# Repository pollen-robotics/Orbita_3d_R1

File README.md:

# Orbita_3d_R1
All you need to make your own Orbita_3d Joint!

## Basically
Please find:
 - Electronic boards that controls (elec_Houston), drives (elec_Major_Tom) and measures (elec_Pacman) the Orbita 3d Joint over 12V-supplied Dynamixel bus.
 - Firmware gather communication (Dynamixel library) and motor control (SimpleFOC library)
 - Cables

## Licences
 - Firmware is under Apache-2.0 licence
 - Electronic/Cables is under CC-BY-SA-NC Licence

## Patents
https://patents.google.com/patent/FR3141363A1

## Contact
contact@pollen-robotics.com

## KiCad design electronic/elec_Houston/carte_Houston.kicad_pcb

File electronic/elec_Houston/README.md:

# Houston Electronic Board

Houston board is basically a STM32G4 microcontroller that focuses on driving 3 BLDC motors. It gets 3 Hall effects or encoders on motors and absolute positions behind reduction through SPI encoders.

<div align="center"></div>

## Basically
 - 50 x 54 mm
 - Powered in 3V3 through the large flat flexible connector J10
 - 5V should also be provided since it supplies encoders J11/21/31
 - Designed with KiCAD 6.0

## ST configuration

<div align="center"></div>

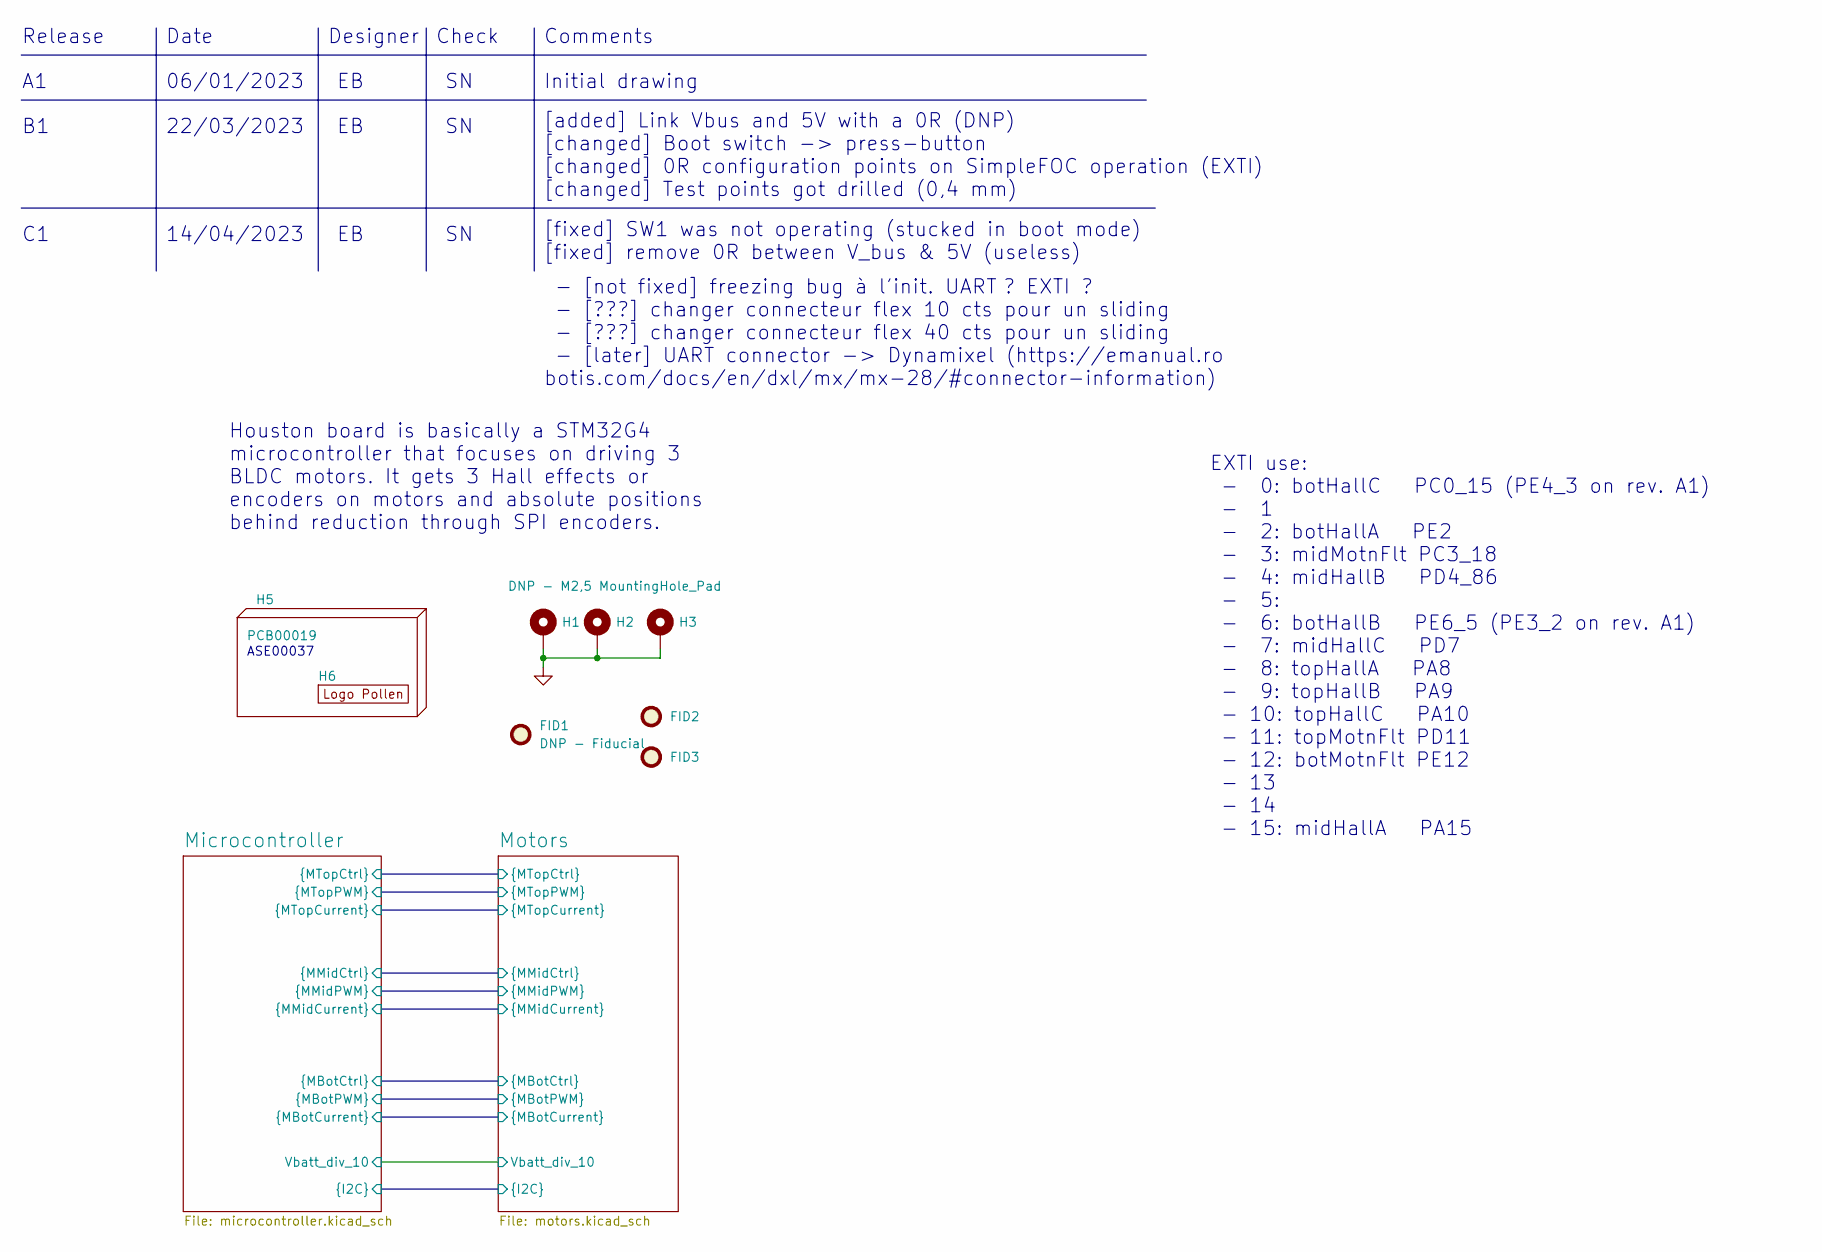
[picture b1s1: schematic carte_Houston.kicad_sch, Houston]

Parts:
FID1, FID2, FID3: DNP - Fiducial; Fiducial_1mm_Mask2mm
H1, H2, H3: DNP - M2,5 MountingHole_Pad; MountingHole_2.7mm_M2.5_DIN965_Pad_TopOnly
H5: PCB00019
H6: DNP - Logo Pollen 2021; Logo_Pollen_2021

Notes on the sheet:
Date
Check
Release
[added] Link Vbus and 5V with a 0R (DNP) [changed] Boot switch -> press-button [changed] 0R configuration points on SimpleFOC operation (EXTI) [changed] Test points got drilled (0,4 mm)
ASE00037
22/03/2023
- [not fixed] freezing bug à l'init. UART ? EXTI ? - [???] changer connecteur flex 10 cts pour un sliding - [???] changer connecteur flex 40 cts pour un sliding - [later] UART connector -> Dynamixel (https://emanual.ro botis.com/docs/en/dxl/mx/mx-28/#connector-information)
Initial drawing
[fixed] SW1 was not operating (stucked in boot mode) [fixed] remove 0R between V_bus & 5V (useless)
EXTI use: - 0: botHallC PC0_15 (PE4_3 on rev. A1) - 1 - 2: botHallA PE2 - 3: midMotnFlt PC3_18 - 4: midHallB PD4_86 - 5: - 6: botHallB PE6_5 (PE3_2 on rev. A1) - 7: midHallC PD7 - 8: topHallA PA8 - 9: topHallB PA9 - 10: topHallC PA10 - 11: topMotnFlt PD11 - 12: botMotnFlt PE12 - 13 - 14 - 15: midHa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
Designer
14/04/2023
Houston board is basically a STM32G4 microcontroller that focuses on driving 3 BLDC motors. It gets 3 Hall effects or encoders on motors and absolute positions behind reduction through SPI encoders.
Comments
06/01/2023

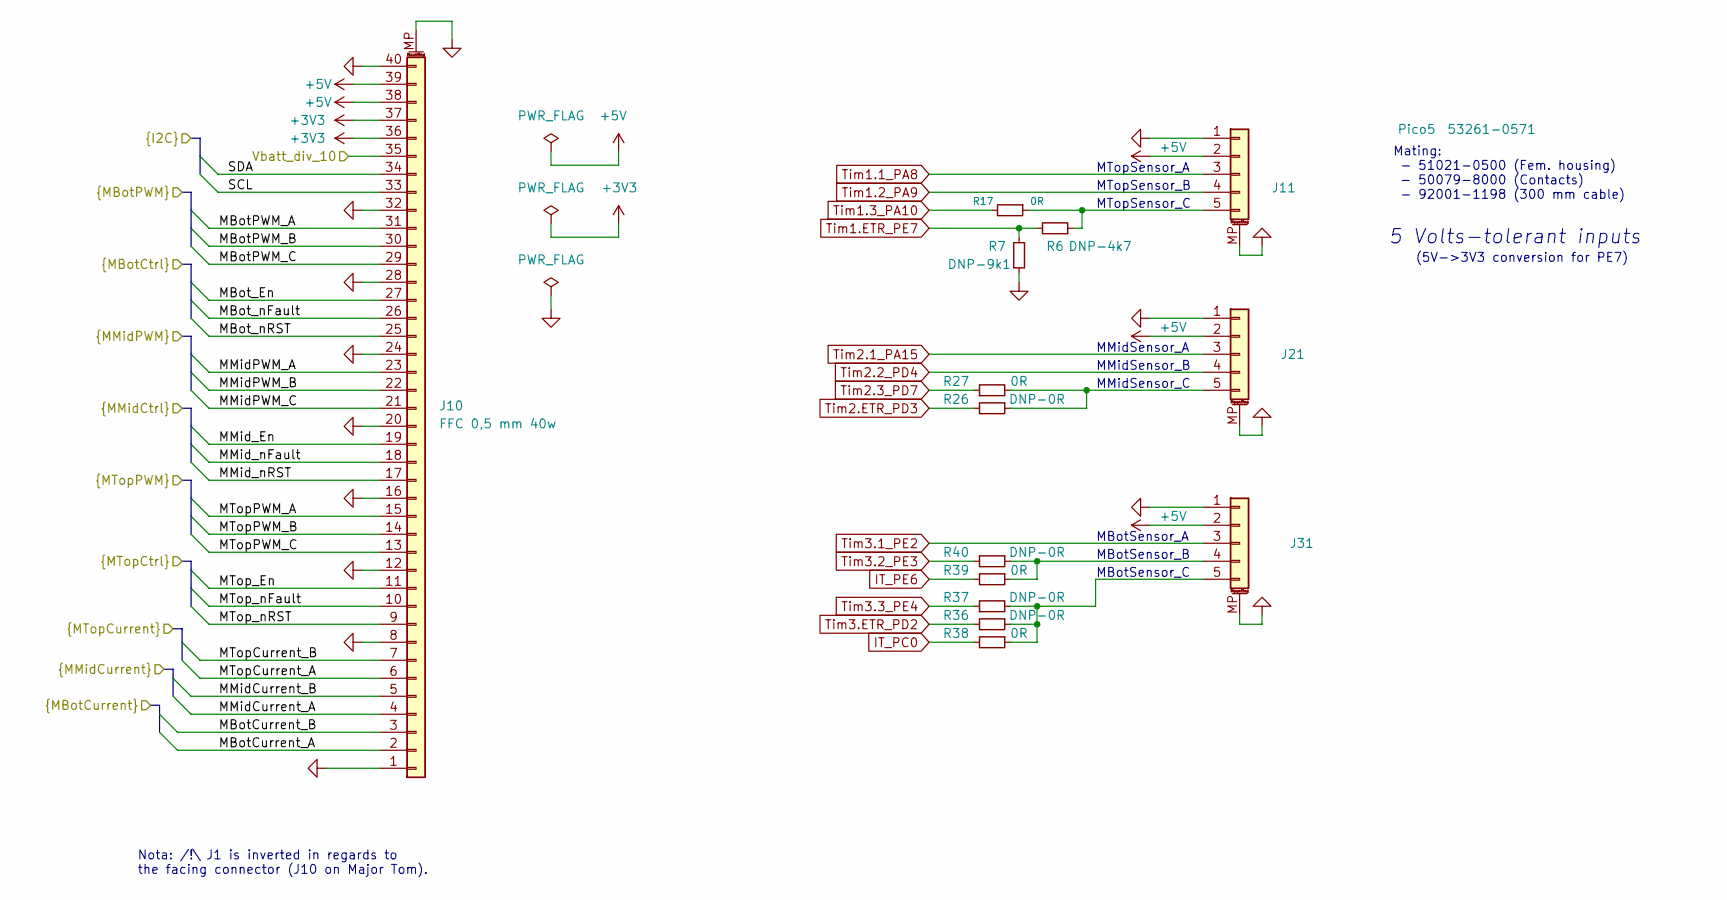
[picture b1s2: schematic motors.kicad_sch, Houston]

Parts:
J10: FFC 0,5 mm 40w; Hirose_FH12-40S-0.5SH_1x40-1MP_P0.50mm_Horizontal
J11: PicoBlade5; Molex_PicoBlade_53261-0571_1x05-1MP_P1.25mm_Horizontal
J21, J31: Pico5; Molex_PicoBlade_53261-0571_1x05-1MP_P1.25mm_Horizontal
R6: DNP-4k7; R_0603_1608Metric
R7: DNP-9k1; R_0603_1608Metric
R17, R27, R38, R39: 0R; R_0603_1608Metric
R26, R36, R37, R40: DNP-0R; R_0603_1608Metric

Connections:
+5V: J10.38, J10.39, J11.2, J21.2, J31.2
/Microcontroller/MBotCurrent_A: J10.2; also elsewhere on the board
/Microcontroller/MBotCurrent_B: J10.3; also elsewhere on the board
/Microcontroller/MBotPWM_A: J10.31; also elsewhere on the board
/Microcontroller/MBotPWM_B: J10.30; also elsewhere on the board
/Microcontroller/MBotPWM_C: J10.29; also elsewhere on the board
/Microcontroller/MBot_En: J10.27; also elsewhere on the board
/Microcontroller/MBot_nFault: J10.26; also elsewhere on the board
/Microcontroller/MBot_nRST: J10.25; also elsewhere on the board
/Microcontroller/MMidCurrent_A: J10.4; also elsewhere on the board
/Microcontroller/MMidCurrent_B: J10.5; also elsewhere on the board
/Microcontroller/MMidPWM_A: J10.23; also elsewhere on the board
/Microcontroller/MMidPWM_B: J10.22; also elsewhere on the board
/Microcontroller/MMidPWM_C: J10.21; also elsewhere on the board
/Microcontroller/MMid_En: J10.19; also elsewhere on the board
/Microcontroller/MMid_nFault: J10.18; also elsewhere on the board
/Microcontroller/MMid_nRST: J10.17; also elsewhere on the board
/Microcontroller/MTopCurrent_A: J10.6; also elsewhere on the board
/Microcontroller/MTopCurrent_B: J10.7; also elsewhere on the board
/Microcontroller/MTopPWM_A: J10.15; also elsewhere on the board
/Microcontroller/MTopPWM_B: J10.14; also elsewhere on the board
/Microcontroller/MTopPWM_C: J10.13; also elsewhere on the board
/Microcontroller/MTop_En: J10.11; also elsewhere on the board
/Microcontroller/MTop_nFault: J10.10; also elsewhere on the board
/Microcontroller/MTop_nRST: J10.9; also elsewhere on the board
/Microcontroller/SCL: J10.33; also elsewhere on the board
/Microcontroller/SDA: J10.34; also elsewhere on the board
/Microcontroller/Vbatt_div_10: J10.35; also elsewhere on the board
IT_PC0: R38.2; also elsewhere on the board
IT_PE6: R39.2; also elsewhere on the board
unnamed: J11.5, R6.1, R17.1
unnamed: J21.5, R26.1, R27.2
unnamed: J31.4, R39.1, R40.1
unnamed: J31.5, R36.1, R37.2, R38.1
Tim1.1_PA8: J11.3; also elsewhere on the board
Tim1.2_PA9: J11.4; also elsewhere on the board
Tim1.3_PA10: R17.2; also elsewhere on the board
Tim1.ETR_PE7: R6.2, R7.1; also elsewhere on the board
Tim2.1_PA15: J21.3; also elsewhere on the board
Tim2.2_PD4: J21.4; also elsewhere on the board
Tim2.3_PD7: R27.1; also elsewhere on the board
Tim2.ETR_PD3: R26.2; also elsewhere on the board
Tim3.1_PE2: J31.3; also elsewhere on the board
Tim3.2_PE3: R40.2; also elsewhere on the board
Tim3.3_PE4: R37.1; also elsewhere on the board
Tim3.ETR_PD2: R36.2; also elsewhere on the board

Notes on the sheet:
MTopSensor_B
MBotSensor_A
MBotSensor_C
MTopSensor_C
MMidSensor_A
(5V->3V3 conversion for PE7)
MBotSensor_B
MTopSensor_A
MMidSensor_B
5 Volts-tolerant inputs
Nota: /!\ J1 is inverted in regards to the facing connector (J10 on Major Tom).
Mating: - 51021-0500 (Fem. housing) - 50079-8000 (Contacts) - 92001-1198 (300 mm cable)
MMidSensor_C

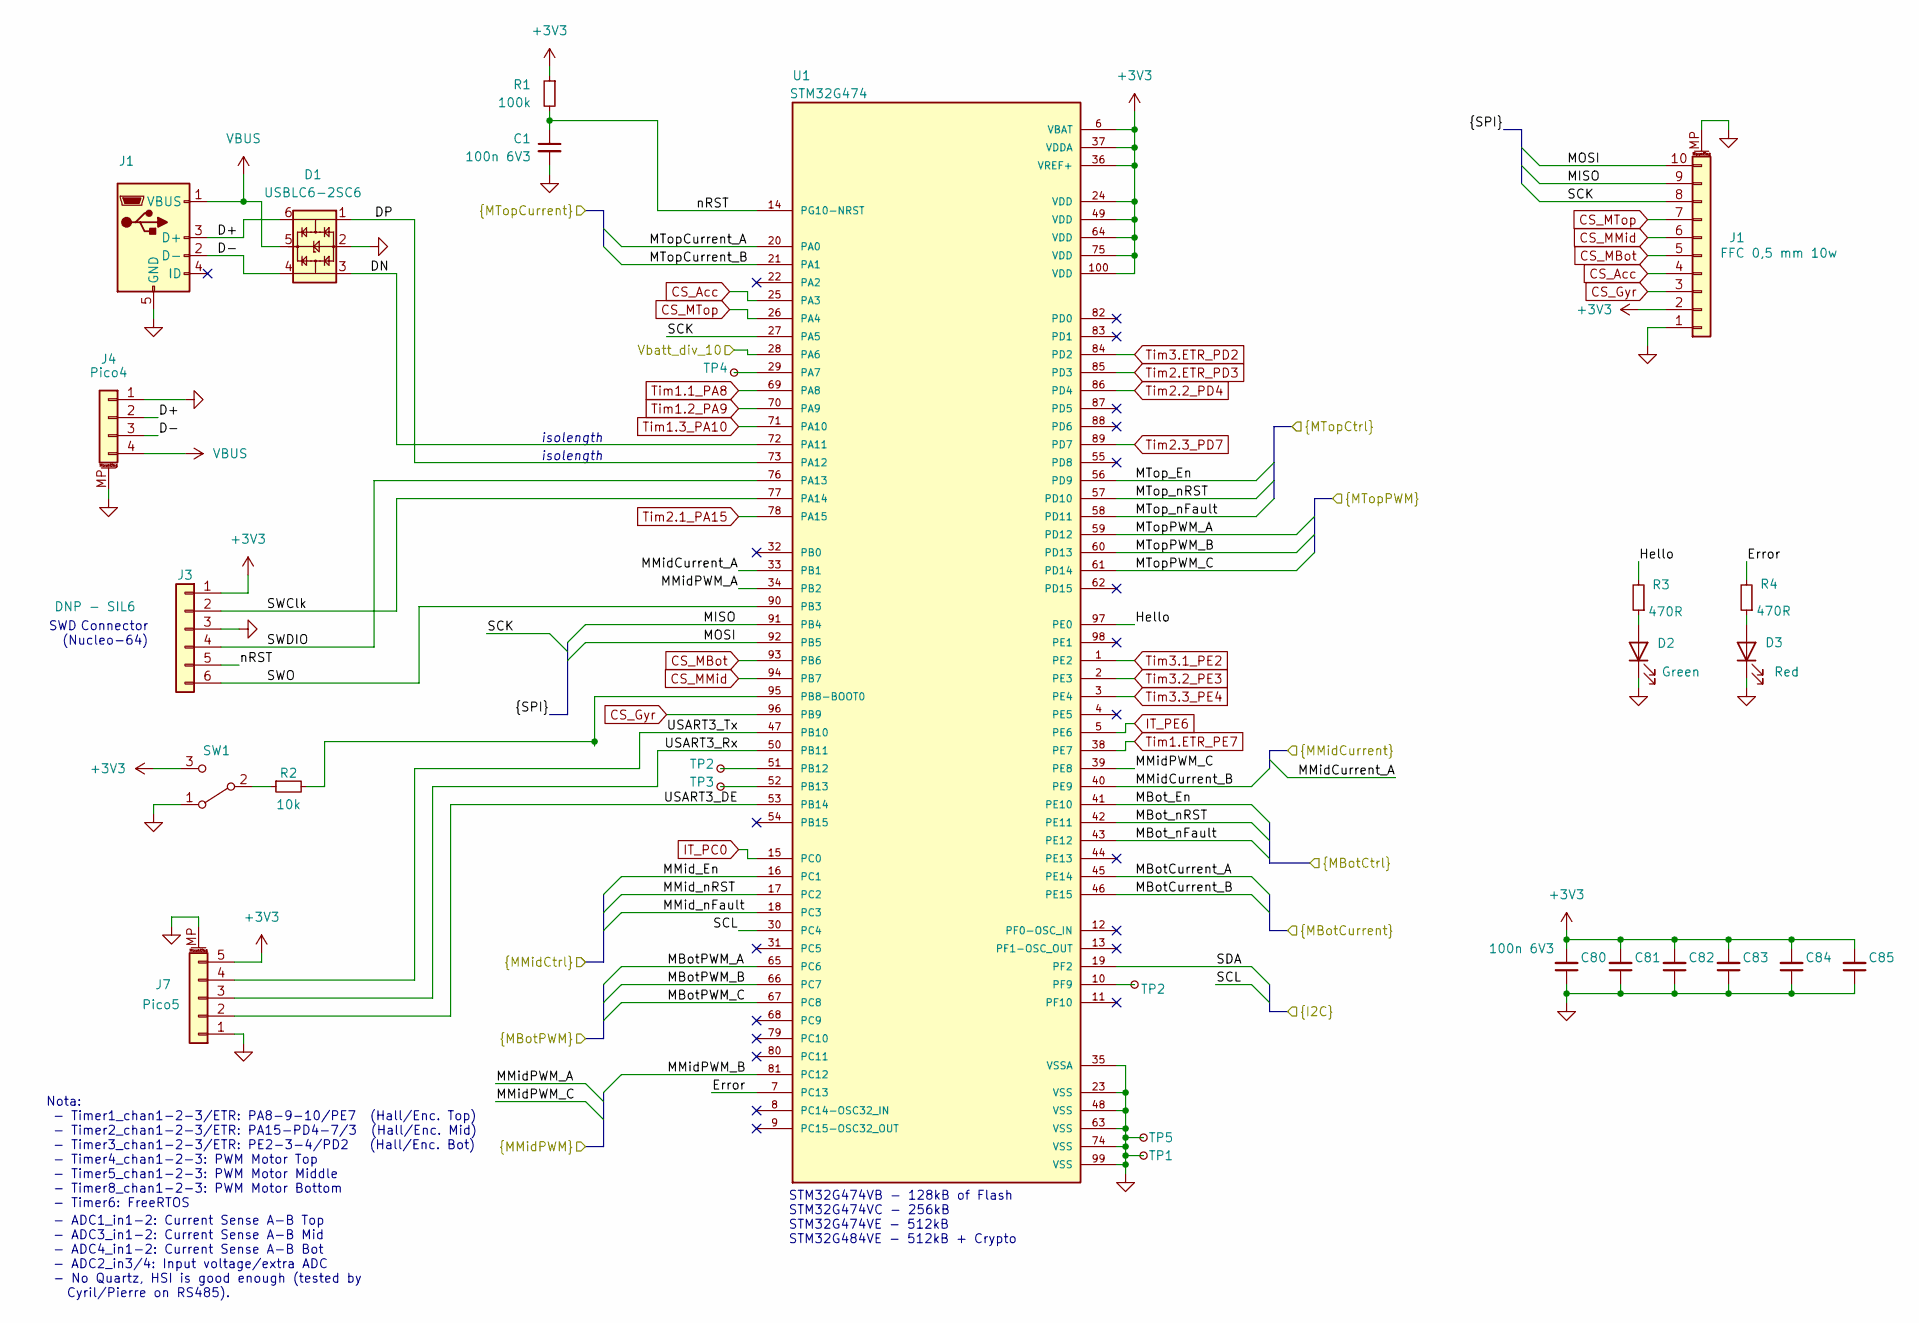
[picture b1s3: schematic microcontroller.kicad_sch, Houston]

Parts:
C1, C80, C81, C82, C83, C84, C85: 100n 6V3; C_0603_1608Metric
D1: USBLC6-2SC6; SOT23-6L
D2: Green; LED_0603_1608Metric_Pad1.05x0.95mm_HandSolder
D3: Red; LED_0603_1608Metric_Pad1.05x0.95mm_HandSolder
J1: 10118194-0001LF; Amphenol_10118194-0001LF
J3: SIL6; PinHeader_1x06_P2.54mm_Vertical_SMD_Pin1Left
J4: PicoBlade4; Molex_PicoBlade_53398-0471_1x04-1MP_P1.25mm_Vertical
J7: PicoBlade5; Molex_PicoBlade_53261-0571_1x05-1MP_P1.25mm_Horizontal
R1: 100k; R_0603_1608Metric
R2: 10k; R_0603_1608Metric
R3, R4: 470R; R_0603_1608Metric
SW1: SW_SPDT; SW_SPDT_CK-JS102011SAQN
TP1: DNP TestPoint_Small; TestPoint_THTPad_2.0x2.0mm_Drill1.0mm
TP2: DNP TestPoint_Small; TestPoint_Pad_D1.0mm
TP3, TP4, TP5: DNP - TestPoint_Small; TestPoint_THTPad_D1.0mm_Drill0.4mm
U1: STM32G474; QFP50P1600X1600X160-100N

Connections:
/Microcontroller/DN: D1.3, U1.72 (PA11)
/Microcontroller/DP: D1.1, U1.73 (PA12)
/Microcontroller/Error: R4.2, U1.7 (PC13)
/Microcontroller/Hello: R3.2, U1.97 (PE0)
/Microcontroller/MBotCurrent_A: U1.45 (PE14); also elsewhere on the board
/Microcontroller/MBotCurrent_B: U1.46 (PE15); also elsewhere on the board
/Microcontroller/MBotPWM_A: U1.65 (PC6); also elsewhere on the board
/Microcontroller/MBotPWM_B: U1.66 (PC7); also elsewhere on the board
/Microcontroller/MBotPWM_C: U1.67 (PC8); also elsewhere on the board
/Microcontroller/MBot_En: U1.41 (PE10); also elsewhere on the board
/Microcontroller/MBot_nFault: U1.43 (PE12); also elsewhere on the board
/Microcontroller/MBot_nRST: U1.42 (PE11); also elsewhere on the board
/Microcontroller/MISO: J1.9, U1.91 (PB4)
/Microcontroller/MMidCurrent_A: U1.33 (PB1); also elsewhere on the board
/Microcontroller/MMidCurrent_B: U1.40 (PE9); also elsewhere on the board
/Microcontroller/MMidPWM_A: U1.34 (PB2); also elsewhere on the board
/Microcontroller/MMidPWM_B: U1.81 (PC12); also elsewhere on the board
/Microcontroller/MMidPWM_C: U1.39 (PE8); also elsewhere on the board
/Microcontroller/MMid_En: U1.16 (PC1); also elsewhere on the board
/Microcontroller/MMid_nFault: U1.18 (PC3); also elsewhere on the board
/Microcontroller/MMid_nRST: U1.17 (PC2); also elsewhere on the board
/Microcontroller/MOSI: J1.10, U1.92 (PB5)
/Microcontroller/MTopCurrent_A: U1.20 (PA0); also elsewhere on the board
/Microcontroller/MTopCurrent_B: U1.21 (PA1); also elsewhere on the board
/Microcontroller/MTopPWM_A: U1.59 (PD12); also elsewhere on the board
/Microcontroller/MTopPWM_B: U1.60 (PD13); also elsewhere on the board
/Microcontroller/MTopPWM_C: U1.61 (PD14); also elsewhere on the board
/Microcontroller/MTop_En: U1.56 (PD9); also elsewhere on the board
/Microcontroller/MTop_nFault: U1.58 (PD11); also elsewhere on the board
/Microcontroller/MTop_nRST: U1.57 (PD10); also elsewhere on the board
/Microcontroller/SCK: J1.8, U1.27 (PA5)
/Microcontroller/SCL: U1.30 (PC4); also elsewhere on the board
/Microcontroller/SDA: U1.19 (PF2); also elsewhere on the board
/Microcontroller/SWClk: J3.2, U1.77 (PA14)
/Microcontroller/SWDIO: J3.4, U1.76 (PA13)
/Microcontroller/SWO: J3.6, U1.90 (PB3)
/Microcontroller/USART3_DE: J7.2, U1.53 (PB14)
/Microcontroller/USART3_Rx: J7.3, U1.50 (PB11)
/Microcontroller/USART3_Tx: J7.4, U1.47 (PB10)
/Microcontroller/Vbatt_div_10: U1.28 (PA6); also elsewhere on the board
/Microcontroller/nRST: C1.1, J3.5, R1.2, U1.14 (PG10-NRST)
CS_Acc: J1.4, U1.25 (PA3)
CS_MMid: J1.6, U1.94 (PB7)
CS_MTop: J1.7, U1.26 (PA4)
IT_PC0: U1.15 (PC0); also elsewhere on the board
IT_PE6: U1.5 (PE6); also elsewhere on the board
unnamed: D2.2 (A), R3.1
unnamed: D3.2 (A), R4.1
unnamed: R2.1, SW1.2 (B)
unnamed: R2.2, U1.95 (PB8-BOOT0)
unnamed: TP3.1, U1.52 (PB13)
unnamed: TP4.1, U1.29 (PA7)
Tim1.1_PA8: U1.69 (PA8); also elsewhere on the board
Tim1.2_PA9: U1.70 (PA9); also elsewhere on the board
Tim1.3_PA10: U1.71 (PA10); also elsewhere on the board
Tim1.ETR_PE7: U1.38 (PE7); also elsewhere on the board
Tim2.1_PA15: U1.78 (PA15); also elsewhere on the board
Tim2.2_PD4: U1.86 (PD4); also elsewhere on the board
Tim2.3_PD7: U1.89 (PD7); also elsewhere on the board
Tim2.ETR_PD3: U1.85 (PD3); also elsewhere on the board
Tim3.1_PE2: U1.1 (PE2); also elsewhere on the board
Tim3.2_PE3: U1.2 (PE3); also elsewhere on the board
Tim3.3_PE4: U1.3 (PE4); also elsewhere on the board
Tim3.ETR_PD2: U1.84 (PD2); also elsewhere on the board

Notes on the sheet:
Nota: - Timer1_chan1-2-3/ETR: PA8-9-10/PE7 (Hall/Enc. Top) - Timer2_chan1-2-3/ETR: PA15-PD4-7/3 (Hall/Enc. Mid) - Timer3_chan1-2-3/ETR: PE2-3-4/PD2 (Hall/Enc. Bot) - Timer4_chan1-2-3: PWM Motor Top - Timer5_chan1-2-3: PWM Motor Middle - Timer8_chan1-2-3: PWM Motor Bottom - Timer6: FreeRTOS
isolength
STM32G474VB - 128kB of Flash STM32G474VC - 256kB STM32G474VE - 512kB STM32G484VE - 512kB + Crypto
SWD Connector (Nucleo-64)
- ADC1_in1-2: Current Sense A-B Top - ADC3_in1-2: Current Sense A-B Mid - ADC4_in1-2: Current Sense A-B Bot - ADC2_in3/4: Input voltage/extra ADC - No Quartz, HSI is good enough (tested by Cyril/Pierre on RS485).

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
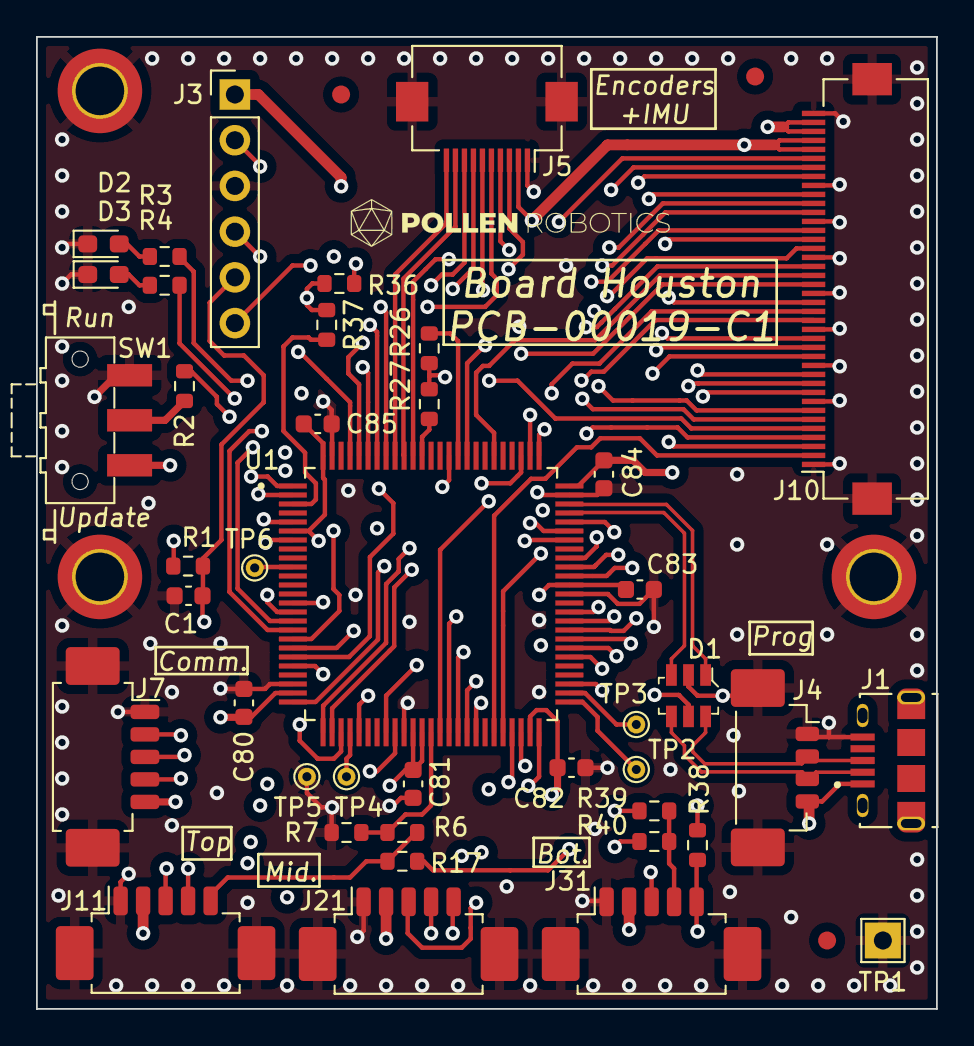
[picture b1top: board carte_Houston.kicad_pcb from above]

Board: 4 copper layers, 50.0 x 54.0 mm, 48 parts (0 on the bottom side), 78 nets.

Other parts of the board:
J1#2: 10118194-0001LF; Amphenol_10118194-0001LF
TP2#2: DNP TestPoint_Small; TestPoint_THTPad_D1.0mm_Drill0.4mm

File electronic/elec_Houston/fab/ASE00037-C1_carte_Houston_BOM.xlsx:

ASE00037 | C1 | Houston | 45030
Ref. | Value | Description | Qtty | Man. | Man. Ref.
C1, C80, C81, C82, C83, C84, C85 | 100n 6V3 | Capa 0603 | 7 | TDK | CGA3E2X7R1H104K080AA
D1 | USBLC6-2SC6 | ESD Protection | 1 | STMicro | USBLC6-2SC6
D2 | Green | Green LED 0603 | 1 | Wurth | 150060VS75000
D3 | Red | Red LED 0603 | 1 | Wurth | 150060RS75000
H5 | PCB00019 | PCB | 1
J1 | 10118194-0001LF | USB Prog Connector | 1 | Amphenol FCI | 10118194-0001LF
J3 | DNP - SIL6 | SWDebug Connector | 1 | Harwin | M20-9990646
J4 | Pico4 | Fake USB Connector | 1 | Molex | 53398-0471
J5 | FFC 0,5 mm 10w | Encoders/IMU Connector | 1 | Hirose | FH12-10S-0.5SH(55)
J7, J11, J21, J31 | Pico5 | Comm. Connector | 4 | Molex | 53261-0571
J10 | FFC 0,5 mm 40w | Microcontroller Connector | 1 | Hirose | FH12-40S-0.5SH(55)
R1 | 100k | Res. 0603 | 1 | Yageo | RC0603FR-07100KL
R2 | 10k | Res. 0603 | 1 | Yageo | RC0603FR-0710KL
R3, R4 | 470R | Res. 0603 | 2 | Yageo | RC0603FR-07470RL
R6 | DNP-4k7 | Res. 0603 | 1
R7 | DNP-9k1 | Res. 0603 | 1
R17, R27, R38, R39 | 0R | Res. 0603 | 4 | Yageo | RC0603FR-070RL
R26, R36, R37, R40 | DNP-0R | Res. 0603 | 4
SW1 | SW_SPDT | Boot switch | 1 | C&K Switches | JS102011SAQN
U1 | STM32G474 | Microcontroller | 1 | STMicro | STM32G474VET6

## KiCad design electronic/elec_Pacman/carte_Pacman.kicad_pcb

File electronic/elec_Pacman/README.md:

# Pacman Electronic Board

Pacman board gathers 3 absolute encoders with an IMU. It is set at the top of the Orbita system and sends angular positions of the 3 axis + IMU data. It is connected to the Houston board through a FFC.

<div align="center"></div>

## Basically
 - 49 mm diameter with a 13 mm slot
 - Powered in 3V3
 - Common SPI, differents CS pins.

## Notas
 - all components are on the bottom side since the encoders are facing down the motors.

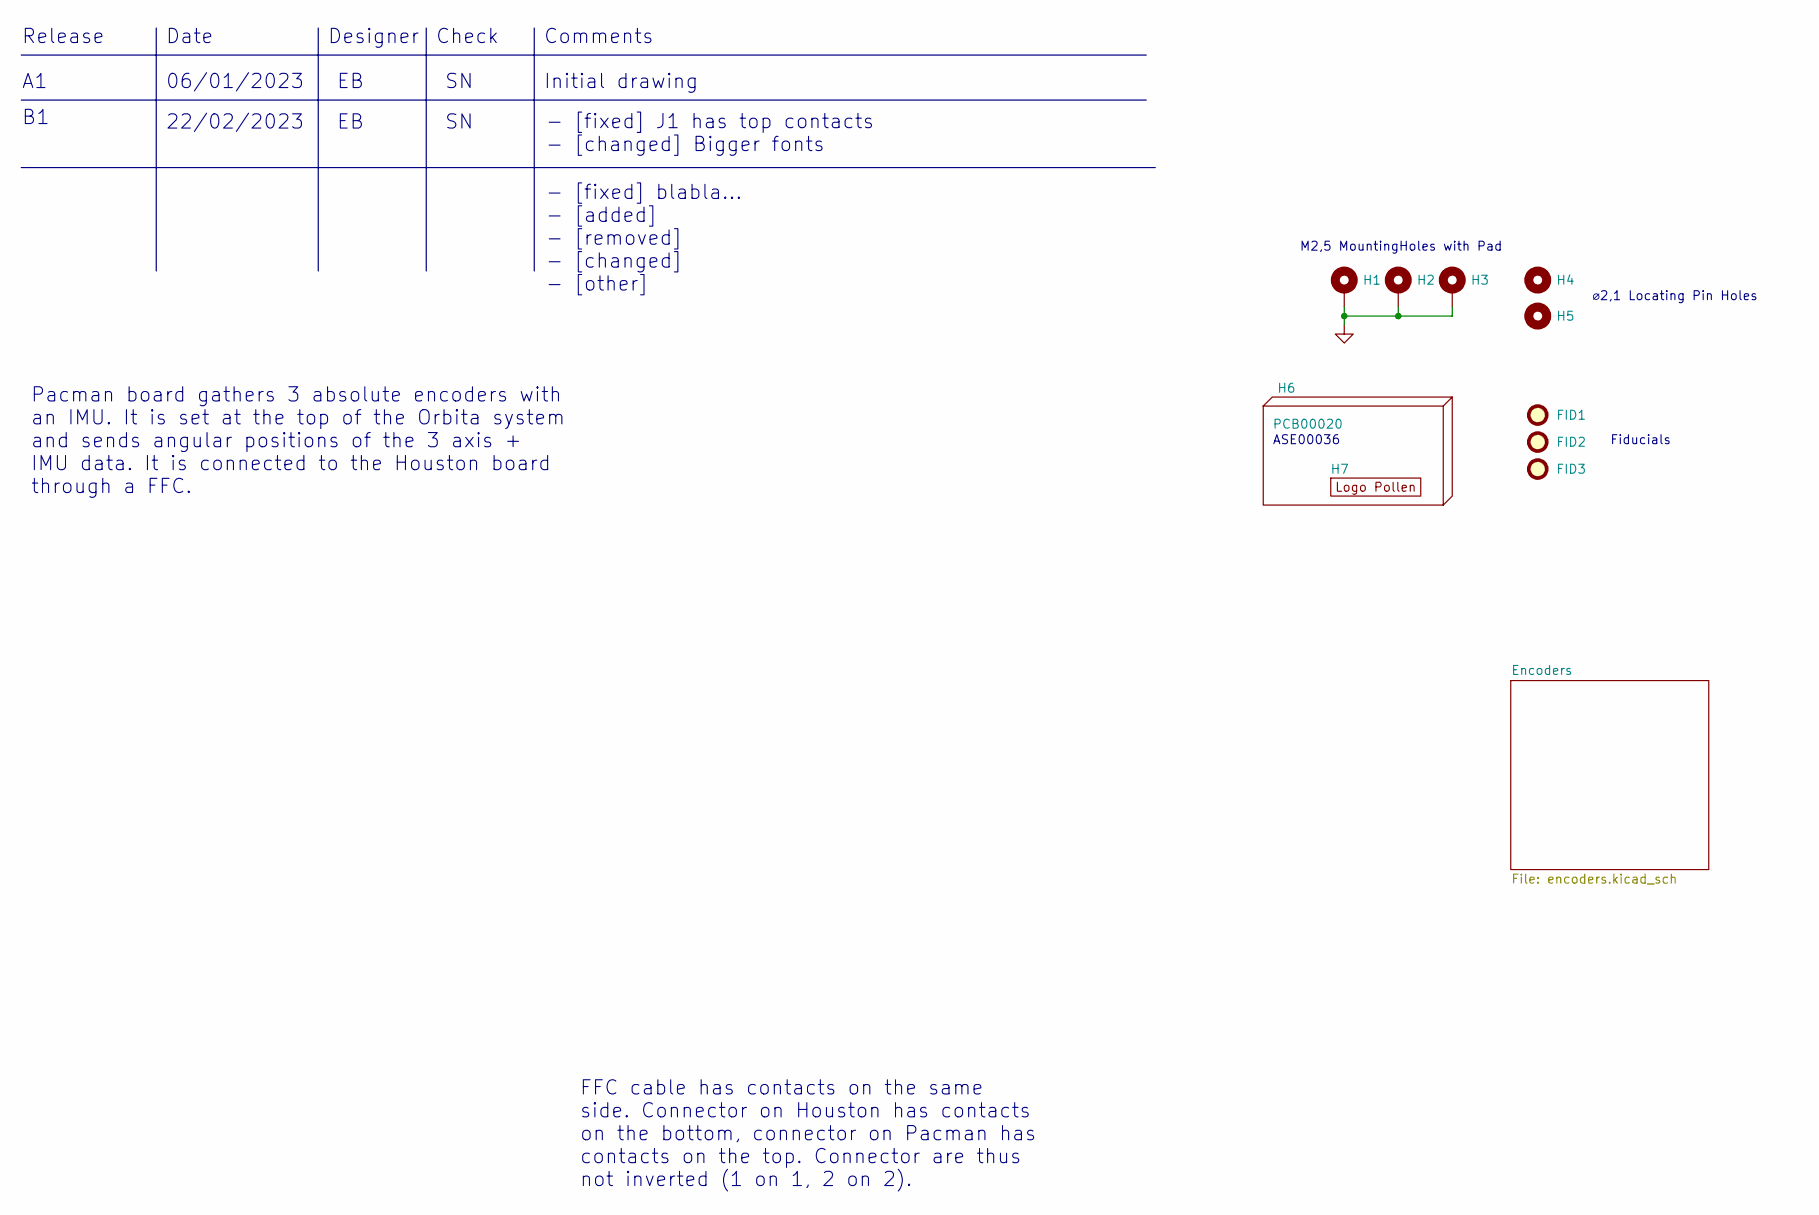
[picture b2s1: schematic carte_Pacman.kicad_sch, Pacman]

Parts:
FID1, FID2, FID3: DNP - Fiducial; Fiducial_0.5mm_Mask1mm
H1, H2: MountingHole_Pad; MountingHole_2.7mm_M2.5_DIN965_Pad_TopBottom
H3: DNP - MountingHole_Pad; MountingHole_2.7mm_M2.5_DIN965_Pad_TopBottom
H4, H5: DNP - LocatingPinHole; MountingHole_2.1mm
H6: PCB00020
H7: DNP Logo Pollen 2021; Logo_Pollen_2021

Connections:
GND: H1.1, H2.1, H3.1; also elsewhere on the board

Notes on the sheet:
M2,5 MountingHoles with Pad
Date
Check
Release
Fiducials
ASE00036
Pacman board gathers 3 absolute encoders with an IMU. It is set at the top of the Orbita system and sends angular positions of the 3 axis + IMU data. It is connected to the Houston board through a FFC.
22/02/2023
Initial drawing
FFC cable has contacts on the same side. Connector on Houston has contacts on the bottom, connector on Pacman has contacts on the top. Connector are thus not inverted (1 on 1, 2 on 2).
Designer
- [fixed] blabla... - [added] - [removed] - [changed] - [other]
- [fixed] J1 has top contacts - [changed] Bigger fonts
Comments
⌀2,1 Locating Pin Holes
06/01/2023

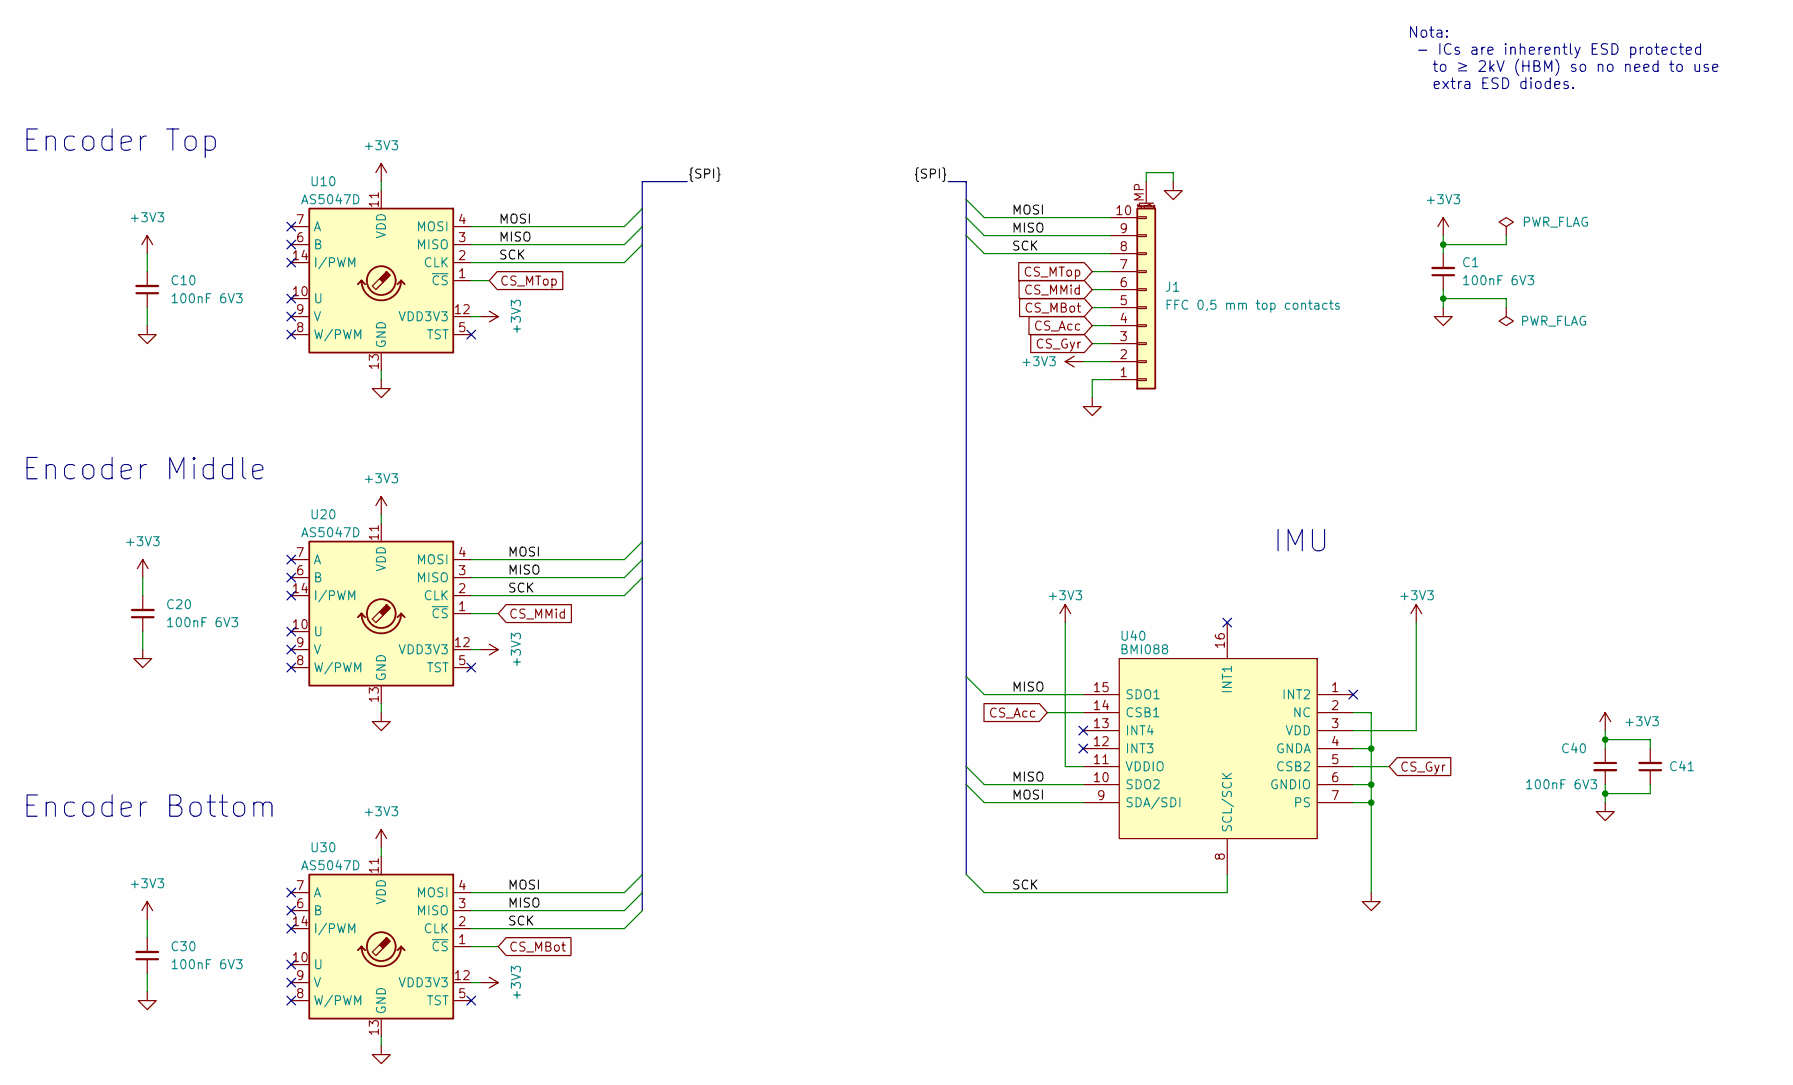
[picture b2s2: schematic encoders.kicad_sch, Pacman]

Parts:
C1, C10, C20, C30, C40, C41: 100nF 6V3; C_0603_1608Metric
J1: Conn_01x10_MountingPin; TE_1-1734839-0
U10, U20, U30: AS5047D; TSSOP-14_4.4x5mm_P0.65mm
U40: BMI088

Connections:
+3V3: C1.2, C10.2, C20.2, C30.2, C40.1, C41.2, J1.2, U10.11 (VDD), U10.12 (VDD3V3), U20.11 (VDD), U20.12 (VDD3V3), U30.11 (VDD), U30.12 (VDD3V3), U40.3 (VDD), U40.11 (VDDIO)
/Encoders/MISO: J1.9, U10.3 (MISO), U20.3 (MISO), U30.3 (MISO), U40.10 (SDO2), U40.15 (SDO1)
/Encoders/MOSI: J1.10, U10.4 (MOSI), U20.4 (MOSI), U30.4 (MOSI), U40.9 (SDA/SDI)
/Encoders/SCK: J1.8, U10.2 (CLK), U20.2 (CLK), U30.2 (CLK), U40.8 (SCL/SCK)
CS_Acc: J1.4, U40.14 (CSB1)
CS_Gyr: J1.3, U40.5 (CSB2)
CS_MBot: J1.5, U30.1 (~CS)
CS_MMid: J1.6, U20.1 (~CS)
CS_MTop: J1.7, U10.1 (~CS)
GND: C1.1, C10.1, C20.1, C30.1, C40.2, C41.1, J1.1, J1.MP (MountPin), U10.13 (GND), U20.13 (GND), U30.13 (GND), U40.2 (NC), U40.4 (GNDA), U40.6 (GNDIO), U40.7 (PS); also elsewhere on the board

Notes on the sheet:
Nota: - ICs are inherently ESD protected to ≥ 2kV (HBM) so no need to use extra ESD diodes.
Encoder Top
Encoder Middle
IMU
Encoder Bottom

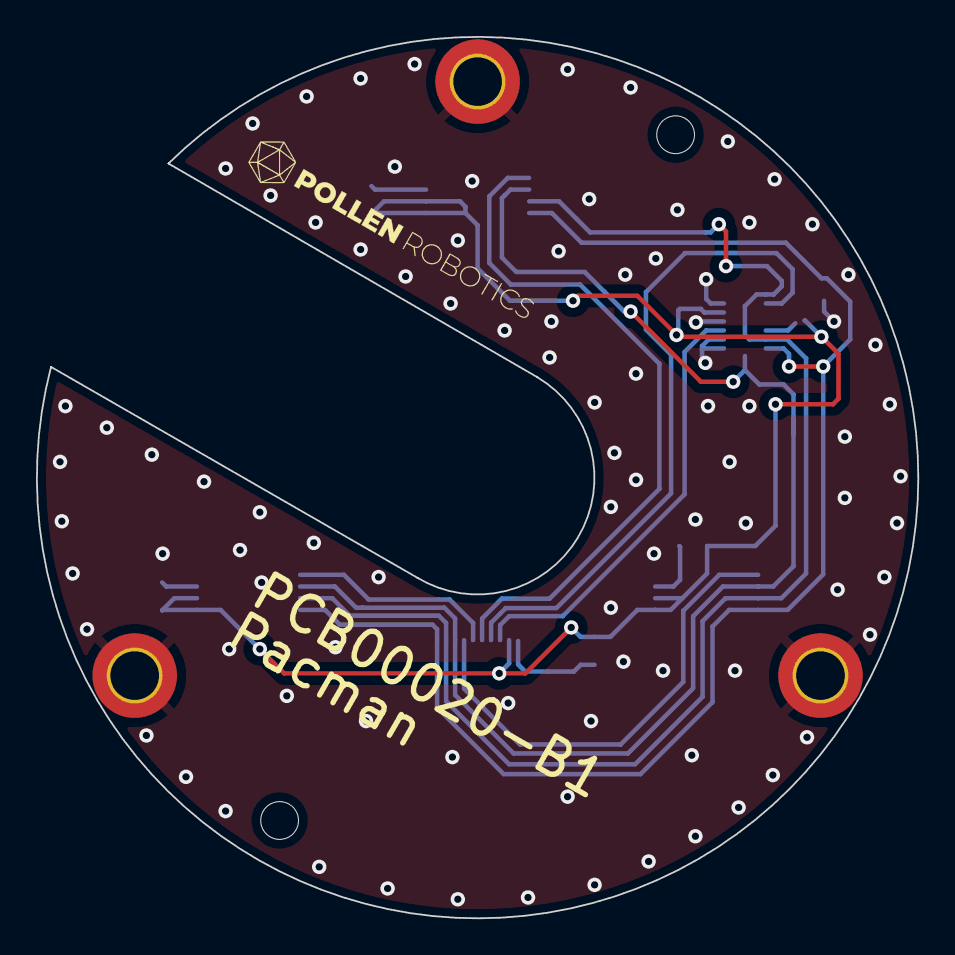
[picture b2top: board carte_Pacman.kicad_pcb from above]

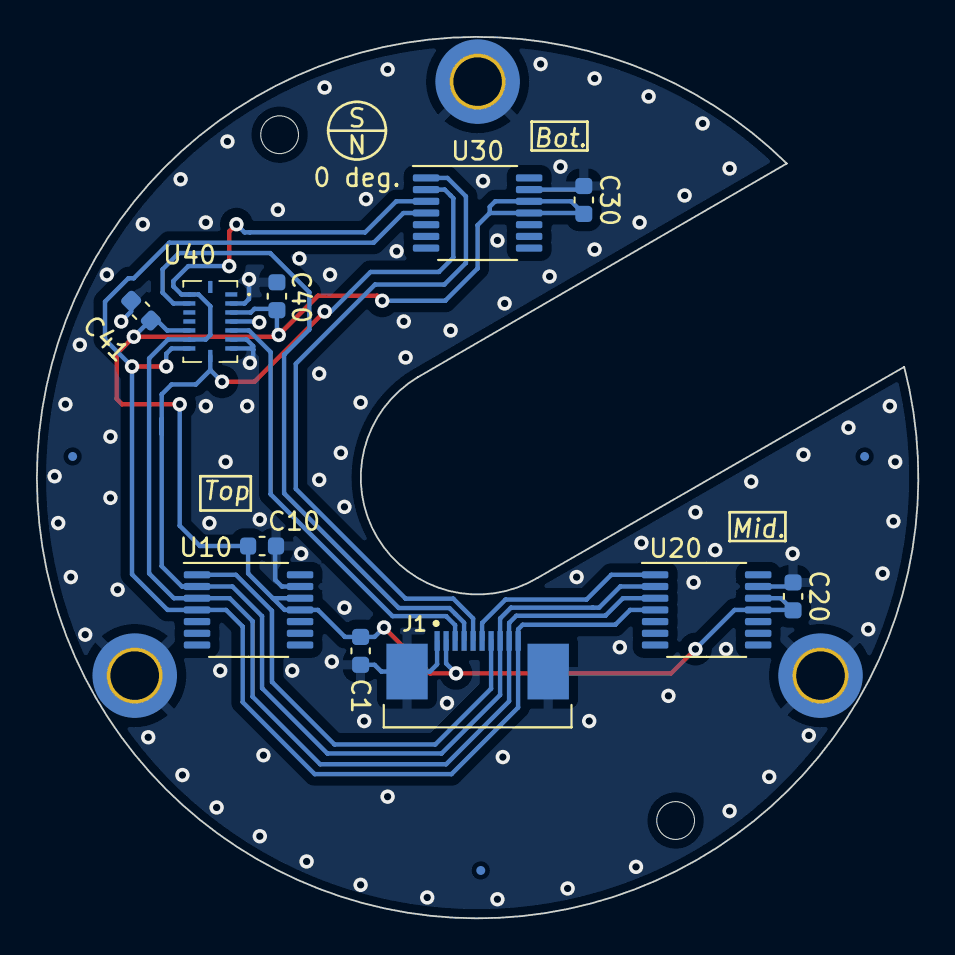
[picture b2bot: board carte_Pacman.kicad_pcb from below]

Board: 2 copper layers, 49.0 x 49.0 mm, 20 parts (14 on the bottom side), 10 nets.

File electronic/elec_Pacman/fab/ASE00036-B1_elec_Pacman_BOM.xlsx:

ASE00036 | B1 | Pacman | 44984
Ref. | Value | Description | Qtty | Man. | Man. Ref.
C1, C10, C20, C30, C40, C41 | 100nF 6V3 | Capa 0603 | 6 | TDK | CGA3E2X7R1H104K080AA
J1 | FFC 0,5 mm top contacts | FFC 0,5mm Connector 10 pins top contacts | 1 | AMP - TE | 1-1734839-0
U10, U20, U30 | AS5047D | Absolute Angular Encoder | 3 | AMS | AS5047D
U40 | BMI088 | Inertial Measurement Unit | 1 | Bosch Sensortec | BMI088
